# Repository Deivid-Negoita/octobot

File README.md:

# Octobot

An eight-legged walking robot with 24 servos, built end to end. The chassis and
legs are CAD. A custom ATmega32U4 board drives every servo. A browser workbench
rigs the CAD model and solves its inverse kinematics.

<sub>Recorded from the live app. [Download the 15-second MP4 with sound](https://github.com/Deivid-Negoita/octobot/raw/main/docs/media/octobot.mp4). Music: Sascha Ende, ende.app (CC BY 4.0), shortened.</sub>

**The workbench runs live in the browser:
<https://deivid-negoita.github.io/octobot/>**. It needs no install and no
build step.

The robot carries environmental-monitoring, 3D-scanning and speleological
payloads. Those payloads need the legs to place feet accurately on uneven
ground, which a fixed gait cannot do. The kinematics workbench in this
repository exists to solve that.

---

## What is here

| Folder | Contents |
|---|---|
| [`kinematics/`](kinematics/) | Browser workbench and locomotion sandbox. Three.js, no build step. |
| [`hardware/`](hardware/) | KiCad 7 project for the 24-channel servo control board. |
| [`mechanical/`](mechanical/) | STEP exports of the chassis and a single leg. |
| [`docs/`](docs/) | [Hardware notes](docs/hardware.md), [kinematics notes](docs/kinematics.md) and the [bill of materials](docs/bom.md). |

The embedded firmware lives in a separate repository and is not included here.

---

## Run the kinematics workbench

The workbench runs in the browser with nothing to install:
**<https://deivid-negoita.github.io/octobot/>**. It is a static site, published
from `kinematics/` by `.github/workflows/pages.yml` on every push to `main`. A
fork gets its own copy after enabling **Settings → Pages → Source → GitHub
Actions** once.

To run it locally instead: the pages load ES modules, so they need an HTTP
server. Opening `index.html` from the filesystem gives you a blank screen and a
CORS error in the console.

```bash
cd kinematics/tools
python serve.py          # or double-click start.bat on Windows
```

Open <http://localhost:8123>. The chassis mesh is about 12 MB, so the first load
takes a few seconds. A progress bar reports the download.

Two pages share the model:

**`index.html`, the IK workbench.** The CAD model rigs itself on startup. The
loader finds the feet from the mesh geometry, then builds a hip-yaw →
shoulder-pitch → knee-pitch chain per leg on the real servo shaft axes. It binds
every servo, bracket and casing to the link it is screwed to. You get eight
chains named `LEG-1` to `LEG-8`. Drag the cyan target and that leg solves toward
it in real time while the servo angles update. Press `Space` to run a gait.

**`playground.html`, the locomotion sandbox.** Drive the robot with `W A S D` over
terrain blocks you spawn and drag. The feet land on the block surface or the
ground by analytic sampling, and the body rides at the average support height.
Live servo angles for all 24 joints stream into the telemetry panel.

| Key | Action |
|---|---|
| `1` / `2` | JOINTS / SOLVE mode (workbench) |
| `Space` | start or stop walking (workbench) |
| `H` | open the help card (workbench) |
| `P` | show or hide the panels (both pages) |
| `W A S D` | walk (playground) |
| `Q` / `E` | lower or raise the body (playground) |
| `Y` | toggle the onboard camera view (playground) |

Read [`docs/kinematics.md`](docs/kinematics.md) for the solver, the collision
guard and the gait model.

---

## The control board

One board drives all 24 servos. An **ATmega32U4** talks over I²C to **two
PCA9685** 16-channel PWM drivers, which gives 32 channels for the 24 servos and
leaves headroom for sensors. An **SY8303** synchronous buck regulator steps the
input down to the 5 V logic rail, and a P-channel MOSFET on the input protects
against reverse polarity.

The 24 servo headers sit on two separate power rails of 12, so the inrush of one
group of legs cannot brown out the other. Each rail has its own 2-cell 9000 mAh
LiPo pack with an XT60 connector and a step-down converter. An **HC-12** radio
module plugs into a 4-pin header on D8 and D9. Running the link on a software UART keeps the
hardware USART free and lets the antenna sit away from the servo wiring. The
board is a 4-layer design with 120 placements, an AVR-ISP header, a DIP switch
and two tactile buttons.

Building 24 servo channels from discrete drivers would have cost more and taken
more board area than the two PCA9685s do.

`hardware/fabrication/` holds the package the board house was sent. It carries
gerbers for all four copper layers, both drill files, the IPC netlist, the
placement file and the BOM. Read [`docs/hardware.md`](docs/hardware.md) for the
rail split, the power path and the pin assignment of every header.

### Bill of materials

120 placements over 33 lines: 87 SMT and 33 through-hole. The table is read out of
the layout by [`hardware/tools/gen_bom.py`](hardware/tools/gen_bom.py) rather
than typed. `--check` re-groups the fabrication BOM the same way and compares it
designator by designator, so this list cannot quietly go stale:

```bash
python hardware/tools/gen_bom.py --check
120 placements match octobot-controller-bom.csv exactly.
```

<!-- BOM:START -->

| Qty | Value | Manufacturer part | Package | Ref | Function |
|---:|---|---|---|---|---|
| 2 | `PCA9685PW/Q900_118` | NXP | SOP65P640X110-28N | U1–U2 | 16-channel 12-bit PWM generator. 12 channels used each, at 0x40 and 0x41. |
| 1 | `ATmega32U4-M` | Microchip | QFN-44-1EP_7x7mm_P0.5mm_EP5.2x5.2mm | U3 | Host MCU. Native USB, 16 MHz crystal, I2C master. |
| 1 | `AVR-ISP` | — | AVR-ISP | U4 | ISP header on D14/D15/D16 and RESET. |
| 1 | `SY8303AIC` | Silergy | SOT65P280X110-8N | IC1 | Synchronous buck. VIN down to the 5.0 V logic rail set by R11/R12. |
| 3 | `LED` | — | LED_0201_0603Metric | D1, D3–D4 | Power, RX and TX indicators. |
| 1 | `4,7 uH` | Wurth Elektronik 7447713047 | 7447714220 | L1 | Buck output inductor. |
| 1 | `Crystal_GND24` | — | CRYSTAL-SMD-5X3.2-4PAD | Y1 | MCU clock, loaded by C1/C3. |
| 1 | `HPZR-C10X` | Nexperia | HPZRC10X | D5 | 10 V regulator diode. Clamps the pass FET gate. |
| 1 | `RQ3E075ATTB` | ROHM Semiconductor | RQ3E075ATTB | Q1 | P-channel MOSFET. Reverse-polarity pass element on the input. |
| 28 | `Conn_01x03_Pin` | — | PinHeader_1x03_P2.54mm_Vertical | J2–J8, J10–J14, J17–J30, J32–J33 | 24 servo headers (GND / rail / signal), 2 rail feeds (J29/J30), 2 analog headers (J32/J33). |
| 4 | `1x2` | — | PinHeader_1x02_P2.54mm_Vertical | J9, J16, J31, J34 | Input power (J9), 5 V taps (J16/J34), I2C breakout (J31). |
| 1 | `47346-0001` | Molex | MOLEX_47346-0001 | J1 | USB micro-B receptacle. Programming and 5 V input. |
| 1 | `Conn_01x04_Pin` | — | PinHeader_1x04_P2.54mm_Vertical | J15 | HC-12 radio header: 5 V, GND, D8, D9. |
| 2 | `TL3365AF180QG` | E-Switch | SW_TL3365AF180QG | S1–S2 | Reset (S1) and user button on D12 (S2). |
| 1 | `DS04-254-2-03BK-SMT` | CUI Devices | DS04254203BKSMT | S3 | 3-position DIP switch on D14/D15/D16. |
| 24 | `220 Ohm` | — | R_0603_1608Metric | R31–R54 | Series resistor on each servo signal line. |
| 20 | `10K` | — | R_0603_1608Metric | R1, R5, R8, R10, R14, R16–R30 | PWM address and OE straps, I2C pull-ups, buck enable. |
| 2 | `1K` | — | R_0402_1005Metric | R7, R9 | LED series resistors. |
| 2 | `22 Ohm` | — | R_0603_1608Metric | R2–R3 | USB D+/D- series termination. |
| 1 | `100K` | — | R_1206_3216Metric | R15 | Pass FET gate pull-down. |
| 1 | `100K Ohm` | — | R_0805_2012Metric | R13 | Buck switching-frequency set resistor. |
| 1 | `10KOhm` | — | R_0603_1608Metric | R4 | RESET pull-up. |
| 1 | `110K Ohm` | — | R_0805_2012Metric | R11 | Buck feedback divider, upper leg. |
| 1 | `15K Ohm` | — | R_0805_2012Metric | R12 | Buck feedback divider, lower leg. |
| 1 | `1KOhm` | — | R_0603_1608Metric | R6 | LED series resistor. |
| 6 | `10uF` | — | C_0805_2012Metric | C4–C5, C18–C19, C22–C23 | Rail decoupling. |
| 2 | `0,1uF` | — | C_0603_1608Metric | C17, C21 | Decoupling. |
| 2 | `18pF` | — | C_0603_1608Metric | C1, C3 | Crystal load capacitors. |
| 2 | `1uF` | — | C_0805_2012Metric | C2, C8 | USB UCAP and buck input decoupling. |
| 2 | `875075161013` | Wurth Elektronik | CAPAE1030X1240N | C6, C9 | Aluminium electrolytic. Bulk storage, one per servo rail. |
| 1 | `0.1uF` | — | C_0805_2012Metric | C7 | AREF decoupling. |
| 1 | `10nF` | — | C_1206_3216Metric | C20 | Buck bootstrap. |
| 1 | `12 pF` | — | C_1206_3216Metric | C16 | Buck feedback feed-forward. |

**120 placements over 33 lines: 87 SMT and 33 through-hole.**

<!-- BOM:END -->

Distributor part numbers are not tracked in the KiCad project, so an assembly
house needs those added at order time.

---

## Mechanical

`mechanical/` holds STEP exports of the assembled chassis and of a single leg.
Every part is 3D printed. The chassis was modelled in Autodesk Fusion 360, and
`kinematics/models/octobot.glb` is the mesh export the web app loads.

STEP files are text and compress to roughly 15% of their size, so the repository
carries the zips and ignores the loose exports. The chassis is 52 MB unpacked
and 7.7 MB zipped. Unzip before opening in CAD:

```bash
cd mechanical
unzip octobot-chassis.step.zip
```

---

## Tooling

`kinematics/tools/` holds the development scripts:

```bash
python serve.py          # static server with caching disabled
python verify.py         # drive both pages in Chromium, fail on any console error
python shots.py          # regenerate the README screenshots
```

`verify.py` and `shots.py` need Playwright:

```bash
pip install playwright && playwright install chromium
```

`verify.py` boots each page and asserts that the rig produced eight legs. It
then exercises the help modal, toggles the panels, runs the gait, spawns a
terrain block and walks the robot. It exits non-zero if the browser logged an
error.

---

## Built with

Three.js 0.160 loaded from a CDN, plain ES modules, no bundler and no
dependencies to install. KiCad 7 for the board. Autodesk Fusion 360 for the
mechanics.

## License

MIT. See [LICENSE](LICENSE).

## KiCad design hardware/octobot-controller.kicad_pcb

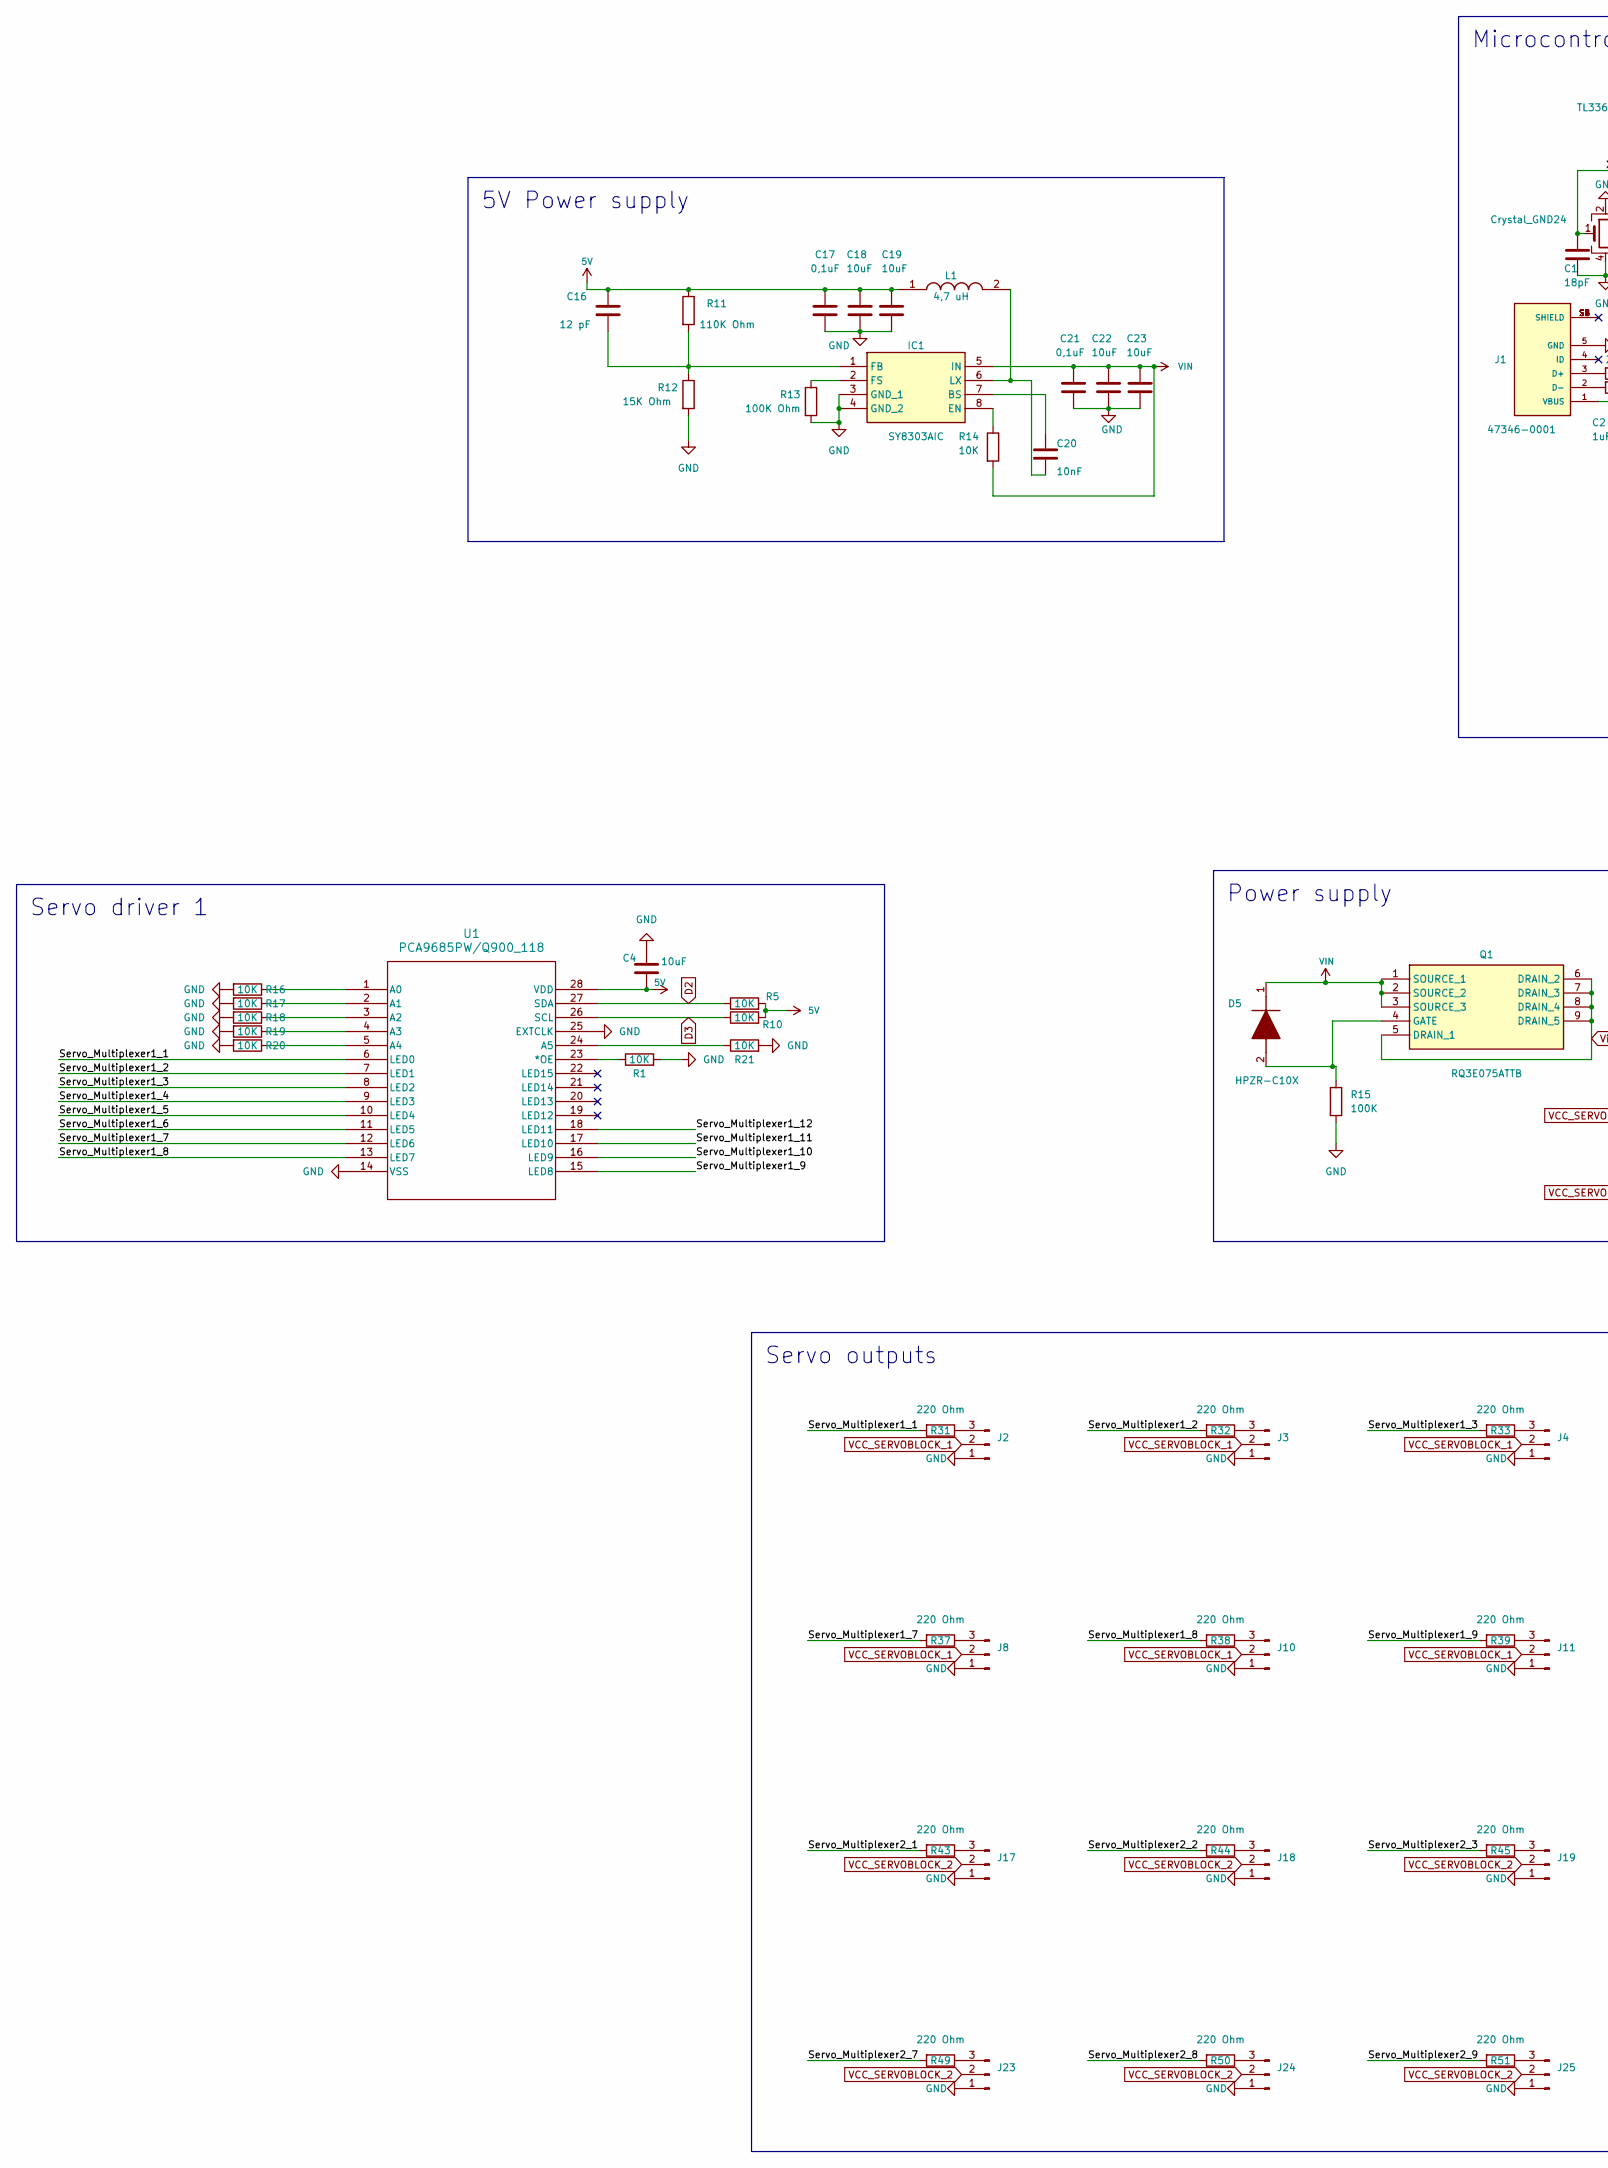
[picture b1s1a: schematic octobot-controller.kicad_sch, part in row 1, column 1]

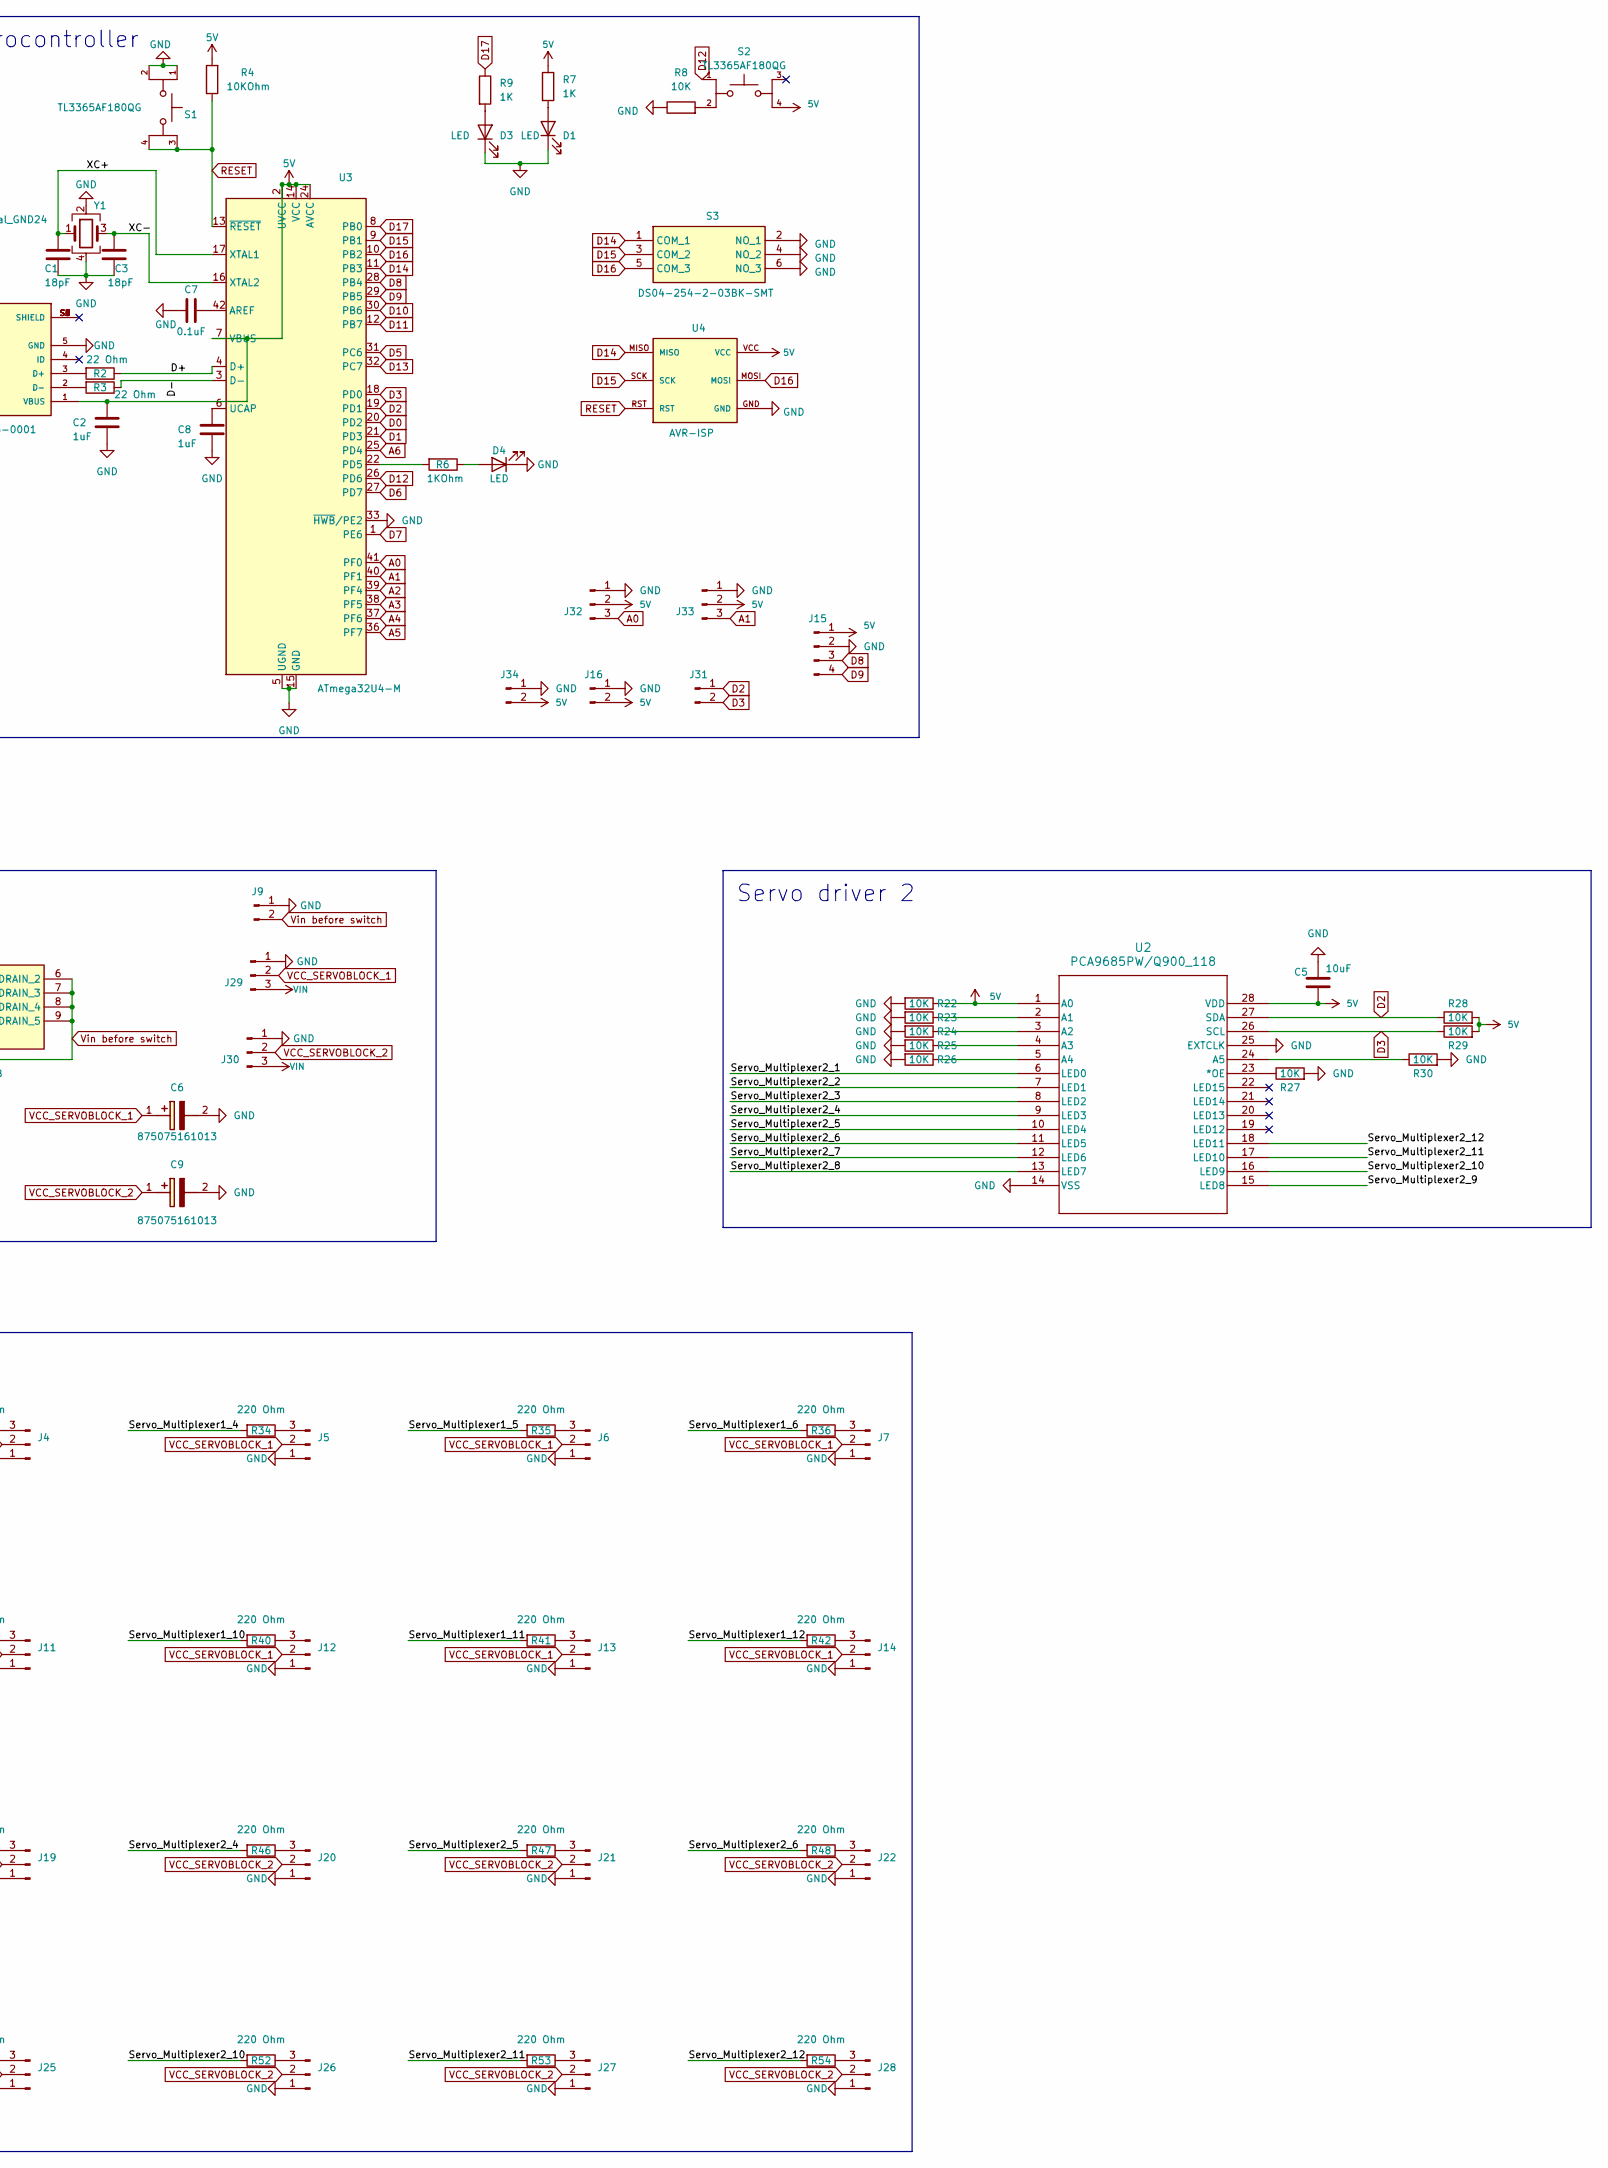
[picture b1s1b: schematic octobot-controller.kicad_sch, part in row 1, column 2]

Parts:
C1, C3: 18pF; C_0603_1608Metric
C2, C8: 1uF; C_0805_2012Metric
C4, C5, C18, C19, C22, C23: 10uF; C_0805_2012Metric
C6, C9: 875075161013; CAPAE1030X1240N; Manufacturer_Part_Number 875075161013; Mouser Part Number 710-875075161013
C7: 0.1uF; C_0805_2012Metric
C16: 12 pF; C_1206_3216Metric
C17, C21: 0,1uF; C_0603_1608Metric
C20: 10nF; C_1206_3216Metric
D1, D3, D4: LED; LED_0201_0603Metric
D5: HPZR-C10X; HPZRC10X; Mouser Part Number 771-HPZR-C10X
IC1: SY8303AIC; SOT65P280X110-8N; Manufacturer_Part_Number SY8303AIC
J1: 47346-0001; MOLEX_47346-0001; PARTREV E
J2, J3, J4, J5, J6, J7, J8, J10, J11, J12, J13, J14, J17, J18, J19, J20, J21, J22, J23, J24, J25, J26, J27, J28, J29, J30, J32, J33: Conn_01x03_Pin; PinHeader_1x03_P2.54mm_Vertical
J9, J16, J31, J34: 1x2; PinHeader_1x02_P2.54mm_Vertical
J15: Conn_01x04_Pin; PinHeader_1x04_P2.54mm_Vertical
L1: 4,7 uH; 7447714220; Mouser Part Number 710-7447713047
Q1: RQ3E075ATTB; Mouser Part Number 755-RQ3E075ATTB
R1, R5, R8, R10, R14, R16, R17, R18, R19, R20, R21, R22, R23, R24, R25, R26, R27, R28, R29, R30: 10K; R_0603_1608Metric
R2, R3: 22 Ohm; R_0603_1608Metric
R4: 10KOhm; R_0603_1608Metric
R6: 1KOhm; R_0603_1608Metric
R7, R9: 1K; R_0402_1005Metric
R11: 110K Ohm; R_0805_2012Metric
R12: 15K Ohm; R_0805_2012Metric
R13: 100K Ohm; R_0805_2012Metric
R15: 100K; R_1206_3216Metric
R31, R32, R33, R34, R35, R36, R37, R38, R39, R40, R41, R42, R43, R44, R45, R46, R47, R48, R49, R50, R51, R52, R53, R54: 220 Ohm; R_0603_1608Metric
S1, S2: TL3365AF180QG; SW_TL3365AF180QG; PARTREV A
S3: DS04-254-2-03BK-SMT; DS04254203BKSMT; Mouser Part Number 490-DS04254203BK-SMT
U1, U2: PCA9685PW/Q900_118; SOP65P640X110-28N
U3: ATmega32U4-M; QFN-44-1EP_7x7mm_P0.5mm_EP5.2x5.2mm
U4: AVR-ISP
Y1: Crystal_GND24; CRYSTAL-SMD-5X3.2-4PAD

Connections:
5V: C2.1, C4.2, C5.2, C16.1, C17.2, C18.1, C19.1, J1.1 (VBUS), J15.1, J16.2, J32.2, J33.2, J34.2, L1.1, R4.2, R5.2, R7.1, R10.2, R11.1, R22.1, R28.2, R29.2, S2.4, U1.28 (VDD), U2.1 (A0), U2.28 (VDD), U3.2 (UVCC), U3.7 (VBUS), U3.14 (VCC), U3.24 (AVCC), U3.34 (VCC), U3.44 (AVCC), U4.VCC
/D+: R2.1, U3.4 (D+)
/D-: R3.1, U3.3 (D-)
/Servo_Multiplexer1_1: R31.2, U1.6 (LED0)
/Servo_Multiplexer1_2: R32.2, U1.7 (LED1)
/Servo_Multiplexer1_3: R33.2, U1.8 (LED2)
/Servo_Multiplexer1_4: R34.2, U1.9 (LED3)
/Servo_Multiplexer1_5: R35.2, U1.10 (LED4)
/Servo_Multiplexer1_6: R36.2, U1.11 (LED5)
/Servo_Multiplexer1_7: R37.2, U1.12 (LED6)
/Servo_Multiplexer1_8: R38.2, U1.13 (LED7)
/Servo_Multiplexer1_9: R39.2, U1.15 (LED8)
/Servo_Multiplexer1_10: R40.2, U1.16 (LED9)
/Servo_Multiplexer1_11: R41.2, U1.17 (LED10)
/Servo_Multiplexer1_12: R42.2, U1.18 (LED11)
/Servo_Multiplexer2_1: R43.2, U2.6 (LED0)
/Servo_Multiplexer2_2: R44.2, U2.7 (LED1)
/Servo_Multiplexer2_3: R45.2, U2.8 (LED2)
/Servo_Multiplexer2_4: R46.2, U2.9 (LED3)
/Servo_Multiplexer2_5: R47.2, U2.10 (LED4)
/Servo_Multiplexer2_6: R48.2, U2.11 (LED5)
/Servo_Multiplexer2_7: R49.2, U2.12 (LED6)
/Servo_Multiplexer2_8: R50.2, U2.13 (LED7)
/Servo_Multiplexer2_9: R51.2, U2.15 (LED8)
/Servo_Multiplexer2_10: R52.2, U2.16 (LED9)
/Servo_Multiplexer2_11: R53.2, U2.17 (LED10)
/Servo_Multiplexer2_12: R54.2, U2.18 (LED11)
/XC+: C1.1, U3.17 (XTAL1), Y1.1
/XC-: C3.1, U3.16 (XTAL2), Y1.3
A0: J32.3, U3.41 (PF0)
A1: J33.3, U3.40 (PF1)
A2: U3.39 (PF4)
A3: U3.38 (PF5)
A4: U3.37 (PF6)
A5: U3.36 (PF7)
A6: U3.25 (PD4)
D0: U3.20 (PD2)
D1: U3.21 (PD3)
D2: J31.1, R5.1, R28.1, U1.27 (SDA), U2.27 (SDA), U3.19 (PD1)
D3: J31.2, R10.1, R29.1, U1.26 (SCL), U2.26 (SCL), U3.18 (PD0)
D5: U3.31 (PC6)
D6: U3.27 (PD7)
D7: U3.1 (PE6)
D8: J15.3, U3.28 (PB4)
D9: J15.4, U3.29 (PB5)
D10: U3.30 (PB6)
D11: U3.12 (PB7)
D12: S2.1, U3.26 (PD6)
D13: U3.32 (PC7)
D14: S3.1 (COM_1), U3.11 (PB3), U4.MISO
D15: S3.3 (COM_2), U3.9 (PB1), U4.SCK
D16: S3.5 (COM_3), U3.10 (PB2), U4.MOSI
D17: R9.1, U3.8 (PB0)
GND: C1.2, C2.2, C3.2, C4.1, C5.1, C6.2 (-), C7.2, C8.2, C9.2 (-), C17.1, C18.2, C19.2, C21.1, C22.2, C23.2, D1.1 (K), D3.1 (K), D4.1 (K), IC1.3 (GND_1), IC1.4 (GND_2), J1.5 (GND), J2.1, J3.1, J4.1, J5.1, J6.1, J7.1, J8.1, J9.1, J10.1, J11.1, J12.1, J13.1, J14.1, J15.2, J16.1, J17.1, J18.1, J19.1, J20.1, J21.1, J22.1, J23.1, J24.1, J25.1, J26.1, J27.1, J28.1, J29.1, J30.1, J32.1, J33.1, J34.1, R1.2, R8.1, R12.2, R13.2, R15.2, R16.2, R17.2, R18.2, R19.2, R20.2, R21.2, R22.2, R23.2, R24.2, R25.2, R26.2, R27.2, R30.2, S1.1, S1.2, S3.2 (NO_1), S3.4 (NO_2), S3.6 (NO_3), U1.14 (VSS), U1.25 (EXTCLK), U2.14 (VSS), U2.25 (EXTCLK), U3.5 (UGND), U3.15 (GND), U3.23 (GND), U3.33 (~HWB/PE2), U3.35 (GND), U3.43 (GND), U3.45 (GND), U4.GND, Y1.2, Y1.4
unnamed: D1.2 (A), R7.2
unnamed: D3.2 (A), R9.2
unnamed: D4.2 (A), R6.1
unnamed: D5.2 (A), Q1.4 (GATE), R15.1
unnamed: C20.1, IC1.7 (BS)
unnamed: IC1.8 (EN), R14.1
unnamed: C16.2, IC1.1 (FB), R11.2, R12.1
unnamed: IC1.2 (FS), R13.1
unnamed: C20.2, IC1.6 (LX), L1.2
unnamed: J1.3 (D+), R2.2
unnamed: J1.2 (D-), R3.2
unnamed: J2.3, R31.1
unnamed: J3.3, R32.1
unnamed: J4.3, R33.1
unnamed: J5.3, R34.1
unnamed: J6.3, R35.1
unnamed: J7.3, R36.1
unnamed: J8.3, R37.1
unnamed: J10.3, R38.1
unnamed: J11.3, R39.1
unnamed: J12.3, R40.1
unnamed: J13.3, R41.1
unnamed: J14.3, R42.1
unnamed: J17.3, R43.1
unnamed: J18.3, R44.1
unnamed: J19.3, R45.1
unnamed: J20.3, R46.1
unnamed: J21.3, R47.1
unnamed: J22.3, R48.1
unnamed: J23.3, R49.1
unnamed: J24.3, R50.1
unnamed: J25.3, R51.1
unnamed: J26.3, R52.1
unnamed: J27.3, R53.1
unnamed: J28.3, R54.1
unnamed: R8.2, S2.2
unnamed: R1.1, U1.23 (*OE)
unnamed: R16.1, U1.1 (A0)
unnamed: R17.1, U1.2 (A1)
unnamed: R18.1, U1.3 (A2)
unnamed: R19.1, U1.4 (A3)
unnamed: R20.1, U1.5 (A4)
unnamed: R21.1, U1.24 (A5)
unnamed: R27.1, U2.23 (*OE)
unnamed: R23.1, U2.2 (A1)
unnamed: R24.1, U2.3 (A2)
unnamed: R25.1, U2.4 (A3)
unnamed: R26.1, U2.5 (A4)
unnamed: R30.1, U2.24 (A5)
unnamed: C7.1, U3.42 (AREF)
unnamed: R6.2, U3.22 (PD5)
unnamed: C8.1, U3.6 (UCAP)
RESET: R4.1, S1.3, S1.4, U3.13 (~RESET), U4.RST
VCC_SERVOBLOCK_1: C6.1 (+), J2.2, J3.2, J4.2, J5.2, J6.2, J7.2, J8.2, J10.2, J11.2, J12.2, J13.2, J14.2, J29.2
VCC_SERVOBLOCK_2: C9.1 (+), J17.2, J18.2, J19.2, J20.2, J21.2, J22.2, J23.2, J24.2, J25.2, J26.2, J27.2, J28.2, J30.2
VIN: C21.2, C22.1, C23.1, D5.1 (K), IC1.5 (IN), J29.3, J30.3, Q1.1 (SOURCE_1), Q1.2 (SOURCE_2), Q1.3 (SOURCE_3), R14.2
Vin before switch: J9.2, Q1.5 (DRAIN_1), Q1.6 (DRAIN_2), Q1.7 (DRAIN_3), Q1.8 (DRAIN_4), Q1.9 (DRAIN_5)

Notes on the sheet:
Servo driver 1
5V Power supply
Microcontroller
Servo driver 2
Power supply
Servo outputs

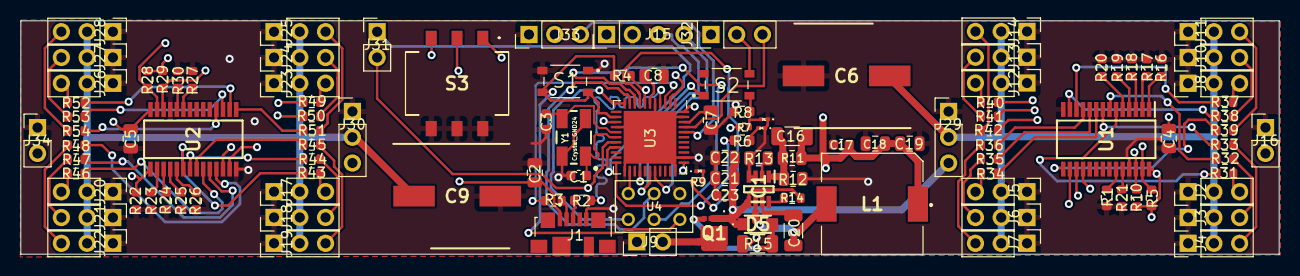
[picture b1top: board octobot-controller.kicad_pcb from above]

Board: 4 copper layers, 124.0 x 23.0 mm, 120 parts (0 on the bottom side), 98 nets.

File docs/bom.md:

# Bill of materials

**Generated from `hardware/octobot-controller.kicad_pcb` by
`hardware/tools/gen_bom.py`. Do not edit by hand.**

The CSVs in `hardware/fabrication/` were exported in 2023 and describe an
earlier board. This table is read from the current layout, so it stays
correct as the board changes. Regenerate it with:

```bash
python hardware/tools/gen_bom.py --write
```

LCSC part numbers are not tracked in the layout, so the fab house needs a
populated CSV before assembly. Export that from KiCad at order time.

---

| Qty | Value | Footprint | Designators |
|---:|---|---|---|
| 28 | `Conn_01x03_Pin` | PinHeader_1x03_P2.54mm_Vertical | J2, J3, J4, J5, J6, J7, J8, J10, J11, J12, J13, J14, J17, J18, J19, J20, J21, J22, J23,... |
| 4 | `1x2` | PinHeader_1x02_P2.54mm_Vertical | J9, J16, J31, J34 |
| 3 | `LED` | LED_0201_0603Metric | D1, D3, D4 |
| 2 | `PCA9685PW/Q900_118` | SOP65P640X110-28N | U1, U2 |
| 2 | `TL3365AF180QG` | SW_TL3365AF180QG | S1, S2 |
| 1 | `4,7 uH` | 7447714220 | L1 |
| 1 | `47346-0001` | MOLEX_47346-0001 | J1 |
| 1 | `ATmega32U4-M` | QFN-44-1EP_7x7mm_P0.5mm_EP5.2x5.2mm | U3 |
| 1 | `AVR-ISP` | AVR-ISP | U4 |
| 1 | `Conn_01x04_Pin` | PinHeader_1x04_P2.54mm_Vertical | J15 |
| 1 | `Crystal_GND24` | CRYSTAL-SMD-5X3.2-4PAD | Y1 |
| 1 | `DS04-254-2-03BK-SMT` | DS04254203BKSMT | S3 |
| 1 | `HPZR-C10X` | HPZRC10X | D5 |
| 1 | `RQ3E075ATTB` | RQ3E075ATTB | Q1 |
| 1 | `SY8303AIC` | SOT65P280X110-8N | IC1 |
| 6 | `10uF` | C_0805_2012Metric | C4, C5, C18, C19, C22, C23 |
| 2 | `0,1uF` | C_0603_1608Metric | C17, C21 |
| 2 | `18pF` | C_0603_1608Metric | C1, C3 |
| 2 | `1uF` | C_0805_2012Metric | C2, C8 |
| 2 | `875075161013` | CAPAE1030X1240N | C6, C9 |
| 1 | `0.1uF` | C_0805_2012Metric | C7 |
| 1 | `10nF` | C_1206_3216Metric | C20 |
| 1 | `12 pF` | C_1206_3216Metric | C16 |
| 24 | `220 Ohm` | R_0603_1608Metric | R31, R32, R33, R34, R35, R36, R37, R38, R39, R40, R41, R42, R43, R44, R45, R46, R47, R4... |
| 20 | `10K` | R_0603_1608Metric | R1, R5, R8, R10, R14, R16, R17, R18, R19, R20, R21, R22, R23, R24, R25, R26, R27, R28, ... |
| 2 | `1K` | R_0402_1005Metric | R7, R9 |
| 2 | `22 Ohm` | R_0603_1608Metric | R2, R3 |
| 1 | `100K` | R_1206_3216Metric | R15 |
| 1 | `100K Ohm` | R_0805_2012Metric | R13 |
| 1 | `10KOhm` | R_0603_1608Metric | R4 |
| 1 | `110K Ohm` | R_0805_2012Metric | R11 |
| 1 | `15K Ohm` | R_0805_2012Metric | R12 |
| 1 | `1KOhm` | R_0603_1608Metric | R6 |

**120 placements, 33 distinct lines.**
